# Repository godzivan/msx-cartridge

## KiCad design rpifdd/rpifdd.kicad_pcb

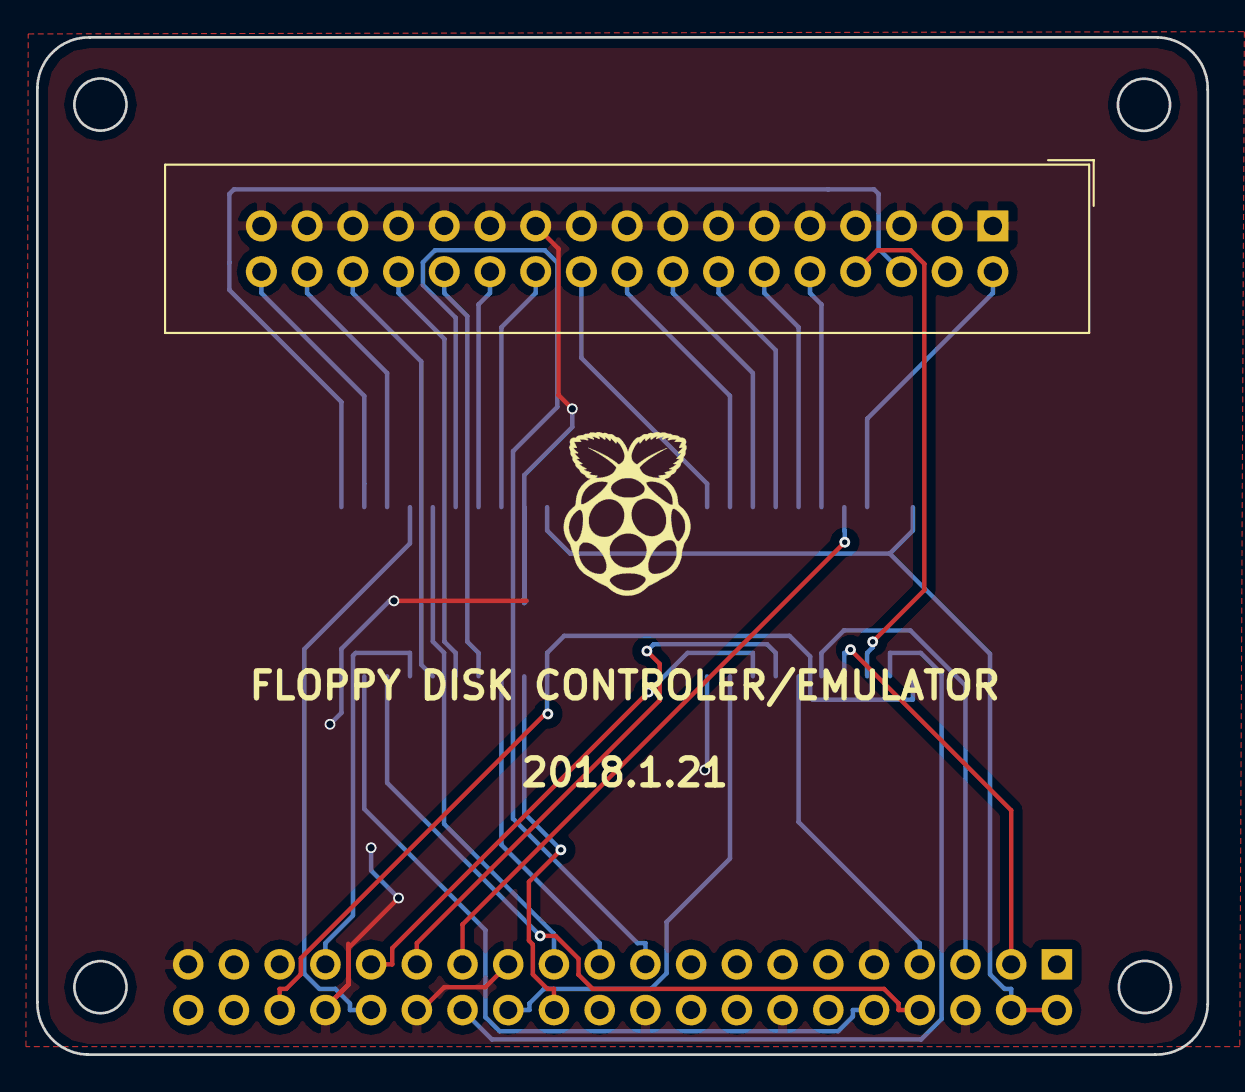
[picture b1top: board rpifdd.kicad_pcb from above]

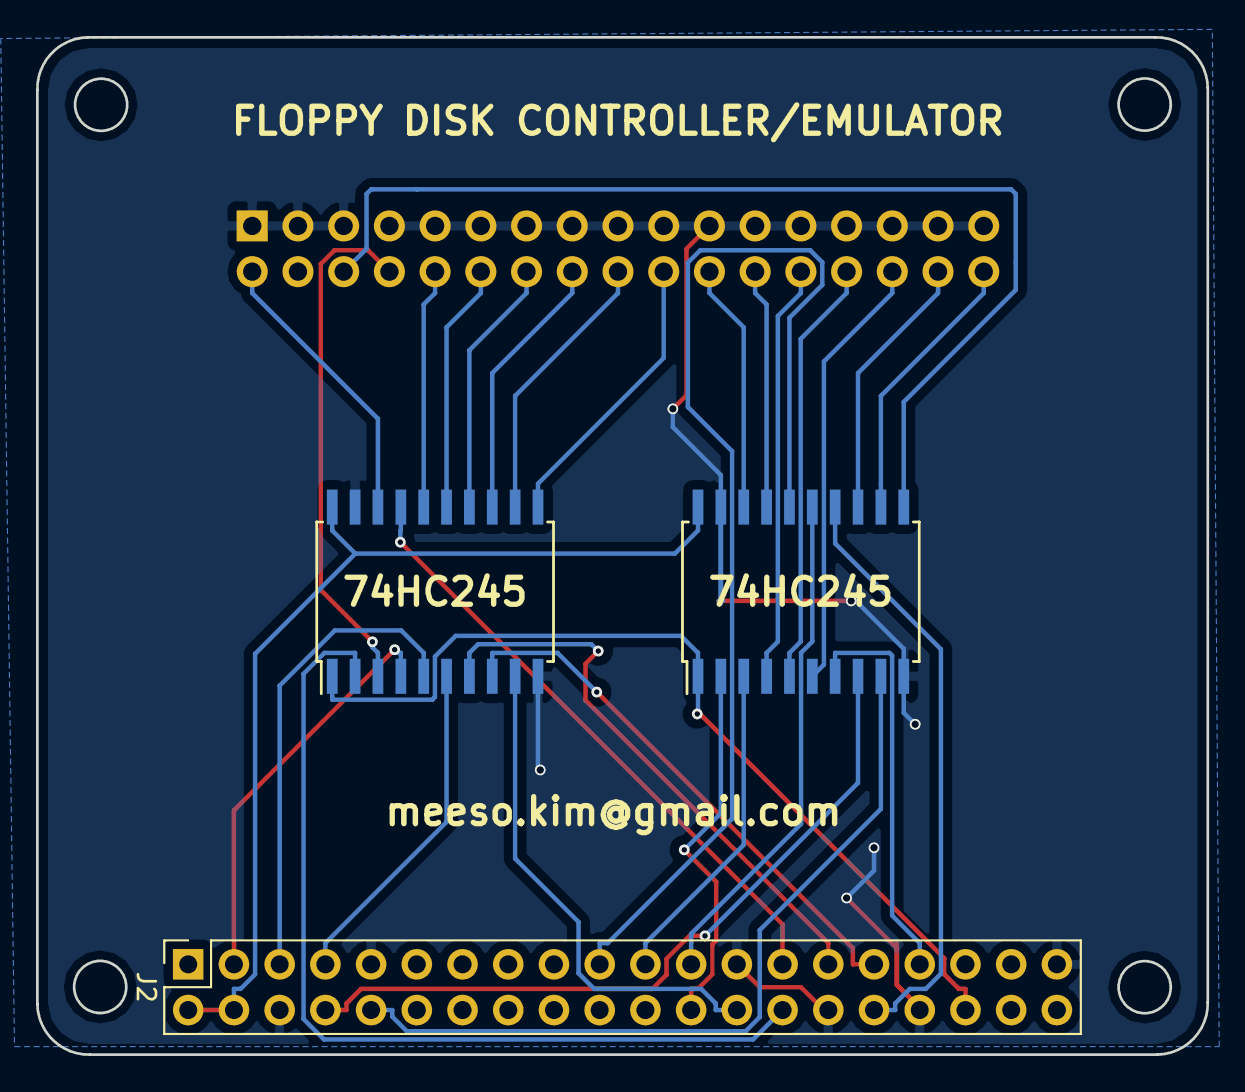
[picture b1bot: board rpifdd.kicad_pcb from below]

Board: 2 copper layers, 65.0 x 56.5 mm, 4 parts (3 on the bottom side), 35 nets.

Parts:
J1: FDD_Connector; IDC-Header_2x17_Pitch2.54mm_Straight
J2: Raspberry_Pi_2_3; Socket_Strip_Straight_2x20_Pitch2.54mm
U1, U2: 74HC245; SOIC-20W_7.5x12.8mm_Pitch1.27mm

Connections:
+5V: J2.2, J2.4, U1.20, U2.20
/DIR: J1.18, U1.12
/DRSEL3: J1.6, U2.11
/DRSELA: J1.12, U1.15
/DRSELB: J1.14, U1.14
/DSKCHG: J1.34, U2.12
/INDEX: J1.8, U1.3
/MODESEL: J1.2, U1.18
/MOTEA: J1.10, U1.16
/MOTEB: J1.16, U1.13
/R0: J2.28, U1.2
/R1: J2.27, U1.17
/R2: J2.3, U1.4
/R3: J2.5, U1.5
/R4: J2.7, U1.6
/R5: J2.29, U1.7
/R6: J2.31, U1.8
/R7: J2.26, U1.9
/R8: J2.24, U2.2
/R9: J2.21, U2.3
/R10: J2.19, U2.16
/R11: J2.23, U2.15
/R12: J2.32, U2.14
/R13: J2.33, U2.7
/R14: J2.8, U2.8
/R15: J2.10, U2.9
/R16: J2.36, U1.1, U2.1
/RDATA: J1.30, U2.6
/SIDE1: J1.32, U2.13
/STEP: J1.20, U1.11
/TRK00: J1.26, U2.4
/WDATA: J1.22, U2.18
/WGATE: J1.24, U2.17
/WPT: J1.28, U2.5
GND: J1.1, J1.3, J1.5, J1.7, J1.9, J1.11, J1.13, J1.15, J1.17, J1.19, J1.21, J1.23, J1.25, J1.27, J1.29, J1.31, J1.33, J2.6, J2.9, J2.14, J2.20, J2.25, J2.30, J2.34, J2.39, U1.10, U1.19, U2.10, U2.19

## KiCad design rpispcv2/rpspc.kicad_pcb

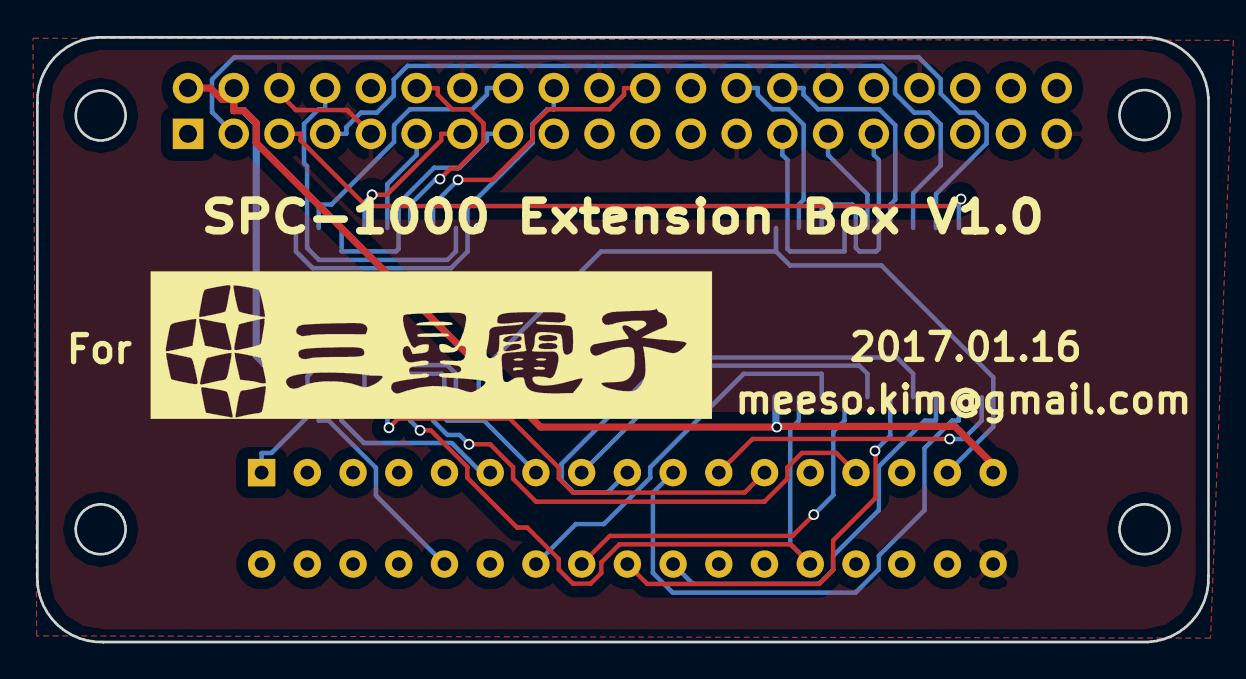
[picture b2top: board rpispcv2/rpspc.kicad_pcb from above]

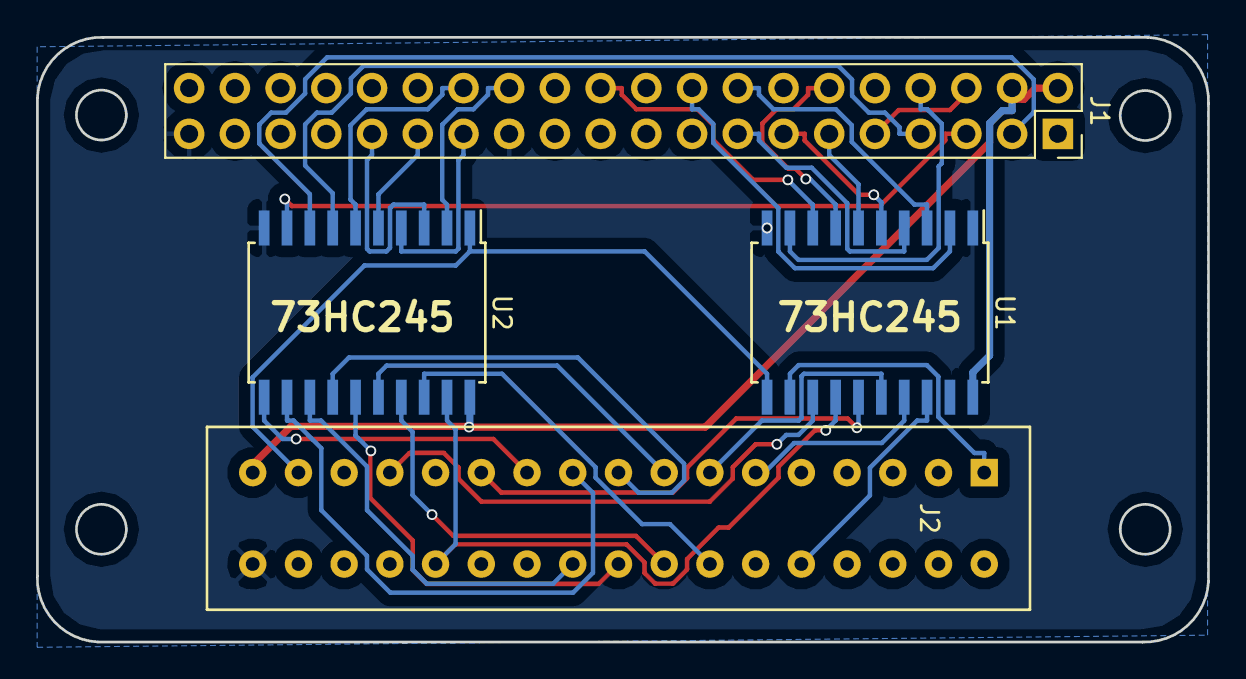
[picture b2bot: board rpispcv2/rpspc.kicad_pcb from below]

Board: 2 copper layers, 65.1 x 33.6 mm, 4 parts (4 on the bottom side), 34 nets.

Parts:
J1: RPi_GPIO; Socket_Strip_Straight_2x20_Pitch2.54mm
J2: Conn_02x17_Top_Bottom; cardedge_female_2x17_2.54mm
U1, U2: 74LS245; SOIC-20W_7.5x12.8mm_Pitch1.27mm

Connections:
+5V: J1.2, J1.4, J2.33, U1.20, U2.20
/A0: J2.13, U1.16
/A1: J2.11, U1.17
/A6: J2.1, U1.12
/A11: J2.10, U1.18
/CLK: J2.27, U1.13
/D0: J2.15, U2.16
/D1: J2.17, U2.14
/D2: J2.19, U2.12
/D3: J2.21, U2.11
/D4: J2.20, U2.13
/D5: J2.18, U2.15
/D6: J2.16, U2.17
/D7: J2.14, U2.18
/EXT1: J2.26, U1.14, U2.19
/RA0: J1.15, U1.4
/RA1: J1.16, U1.3
/RA2: J1.18, U1.2
/RA4: J1.22, U1.8
/RCLK: J1.12, U1.7
/RD0: J1.27, U2.4
/RD1: J1.28, U2.6
/RD2: J1.3, U2.8
/RD3: J1.5, U2.9
/RD4: J1.7, U2.7
/RD5: J1.29, U2.5
/RD6: J1.31, U2.3
/RD7: J1.26, U2.2
/RESET: J2.23, U1.15
/REXT1: J1.11, U1.6
/RRESET: J1.13, U1.5
/RWR: J1.8, U1.9
/WR: J2.31, U1.11, U2.1
GND: J1.6, J1.9, J1.14, J1.20, J1.25, J1.30, J1.34, J1.39, J2.34, U1.1, U1.10, U1.19, U2.10

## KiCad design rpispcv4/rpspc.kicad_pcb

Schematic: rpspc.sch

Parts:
J1, J3: RPi_GPIO; Pin_Header_Straight_2x20_Pitch2.54mm
J2: Conn_02x17_Top_Bottom; Socket_Strip_Straight_2x20_Pitch2.54mm
U1: LVC4245; SOIC-24W_7.5x15.4mm_Pitch1.27mm
U2: 74HC244; SOIC-20W_7.5x12.8mm_Pitch1.27mm

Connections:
+5V: J1.2, J1.4, J2.33, J3.2, J3.4, U1.1
/A0: J2.13, U2.15
/A1: J2.11, U2.13
/A2: J2.9
/A3: J2.7
/A4: J2.5
/A5: J2.3
/A6: J2.1, U2.4
/A7: J2.4
/A8: J2.6
/A9: J2.8
/A10: J2.12
/A11: J2.10, U2.11
/A12: J2.2
/CLK: J2.27, U2.6
/D0: J2.15, U1.8
/D1: J2.17, U1.6
/D2: J2.19, U1.4
/D3: J2.21, U1.3
/D4: J2.20, U1.5
/D5: J2.18, U1.7
/D6: J2.16, U1.9
/D7: J2.14, U1.10
/EXT1: J2.26, U1.22, U2.8
/RA0: J1.15, J3.15, U2.5
/RA1: J1.16, J3.16, U2.7
/RA2: J1.18, J3.18, U2.9
/RA4: J1.22, J3.22, U2.16
/RCLK: J1.12, J3.12, U2.14
/RD: J2.30, U1.2
/RD0: J1.27, J3.27, U1.16
/RD1: J1.28, J3.28, U1.18
/RD2: J1.3, J3.3, U1.20
/RD3: J1.5, J3.5, U1.21
/RD4: J1.7, J3.7, U1.19
/RD5: J1.29, J3.29, U1.17
/RD6: J1.31, J3.31, U1.15
/RD7: J1.26, J3.26, U1.14
/RESET: J2.23, U2.17
/REXT1: J1.11, J3.11, U2.12
/RRESET: J1.13, J3.13, U2.3
/RWR: J1.8, J3.8, U2.18
/VCC: J1.1, J3.1, U1.23, U1.24, U2.20
/WR: J2.31, U2.2
GND: J1.6, J1.9, J1.14, J1.20, J1.25, J1.30, J1.34, J2.34, J3.6, J3.9, J3.14, J3.20, J3.25, J3.30, J3.34, U1.11, U1.12, U1.13, U2.1, U2.10, U2.19

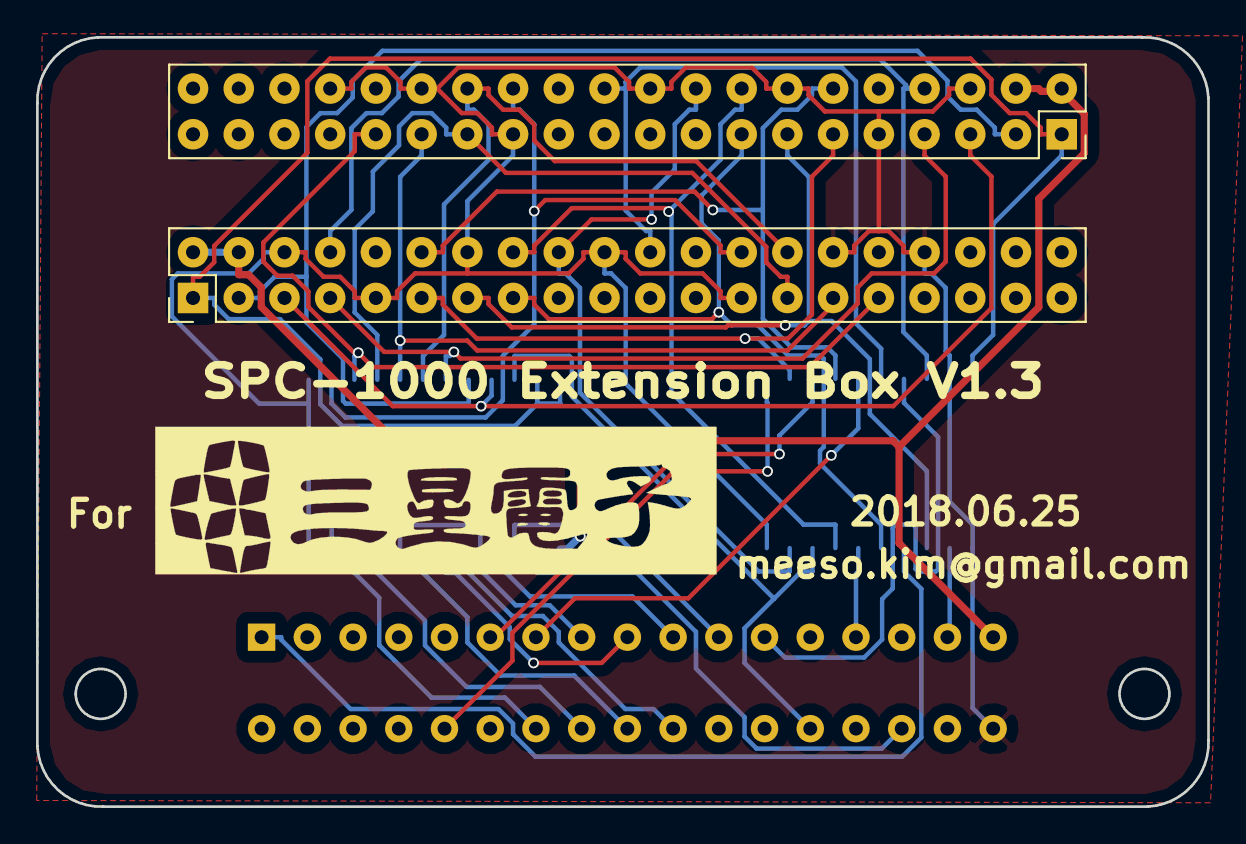
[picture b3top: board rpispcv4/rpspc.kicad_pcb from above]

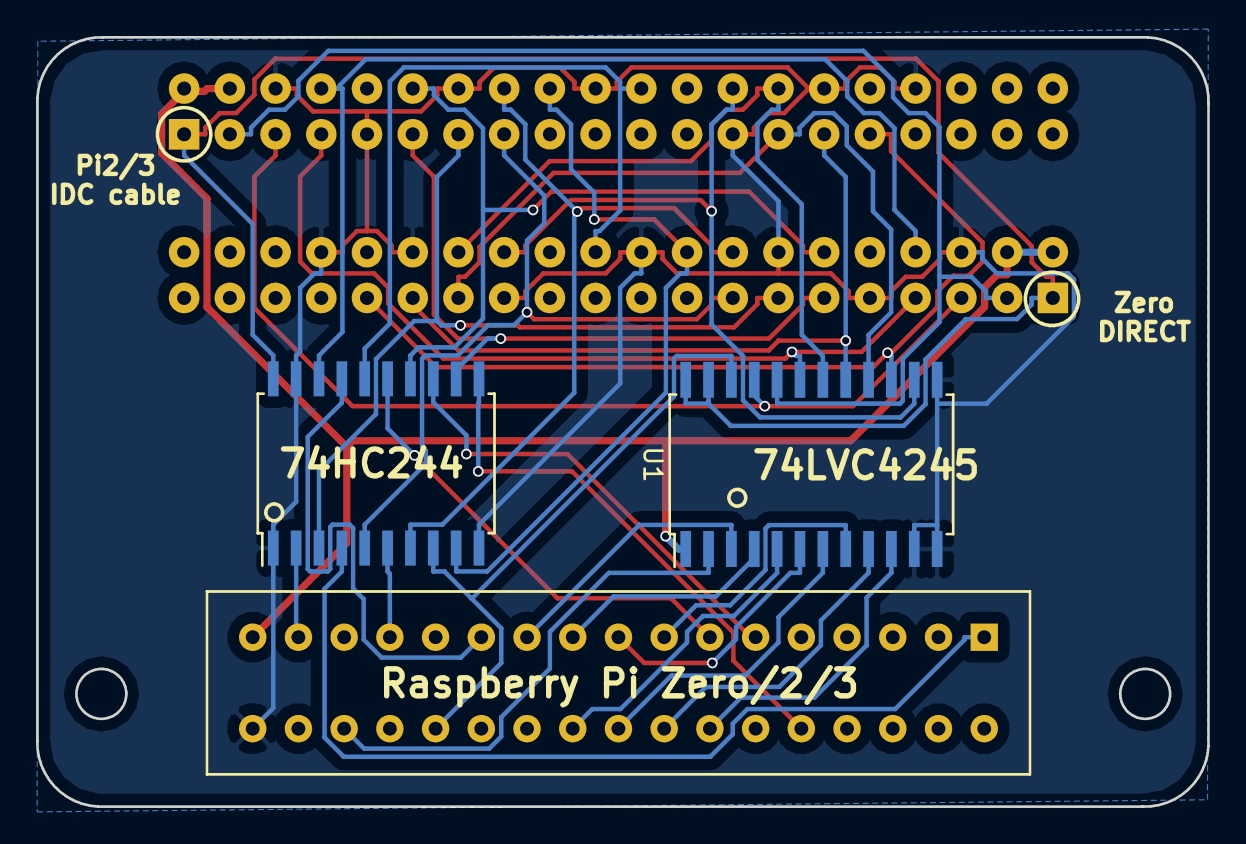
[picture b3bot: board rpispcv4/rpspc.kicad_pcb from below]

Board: 2 copper layers, 65.1 x 42.7 mm, 5 parts (3 on the bottom side), 36 nets.

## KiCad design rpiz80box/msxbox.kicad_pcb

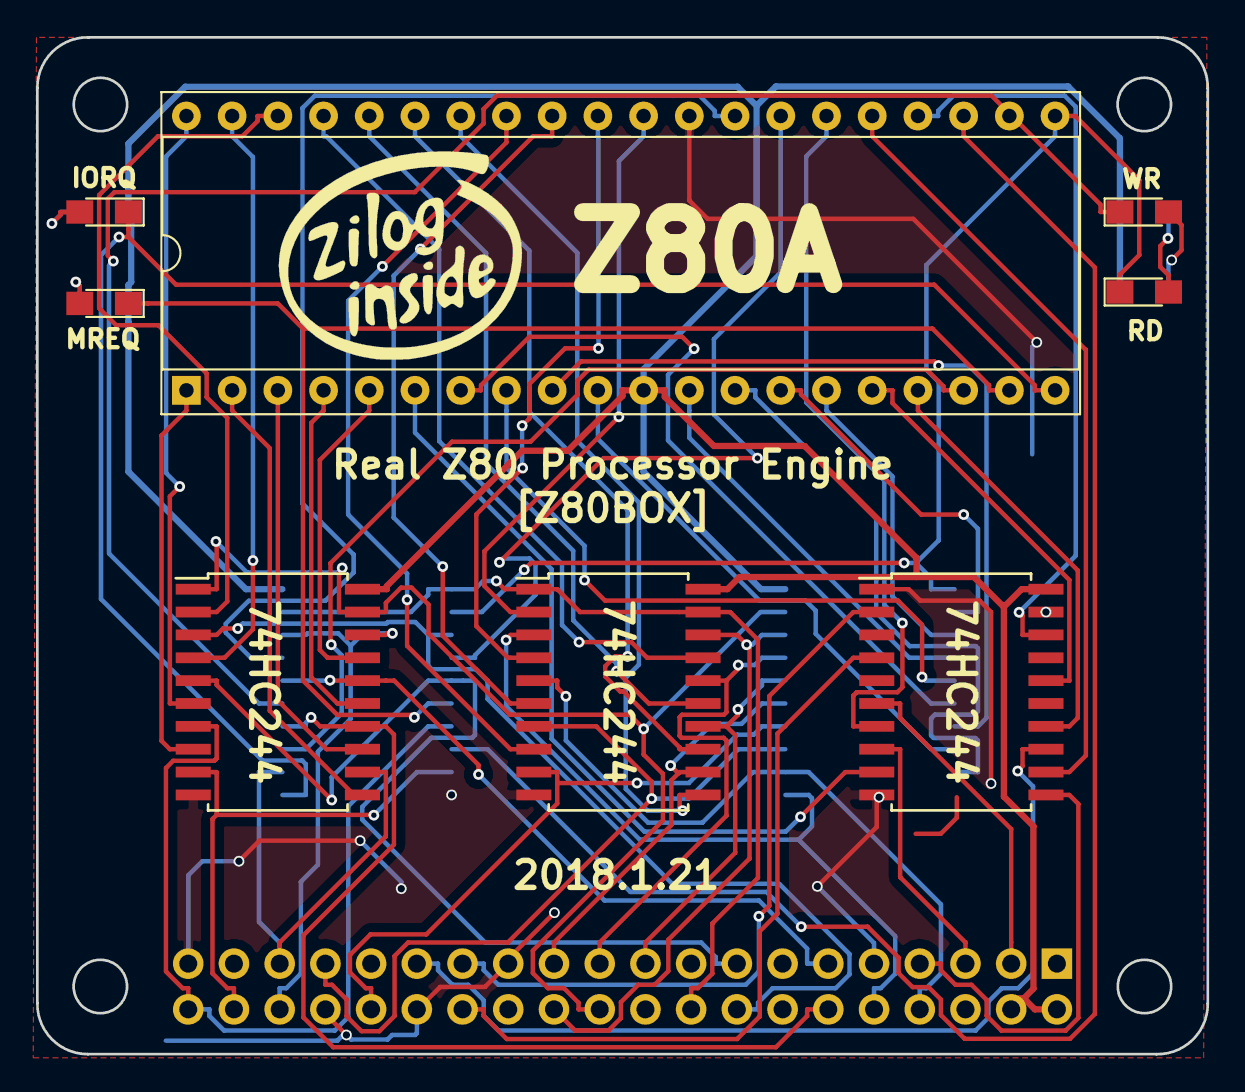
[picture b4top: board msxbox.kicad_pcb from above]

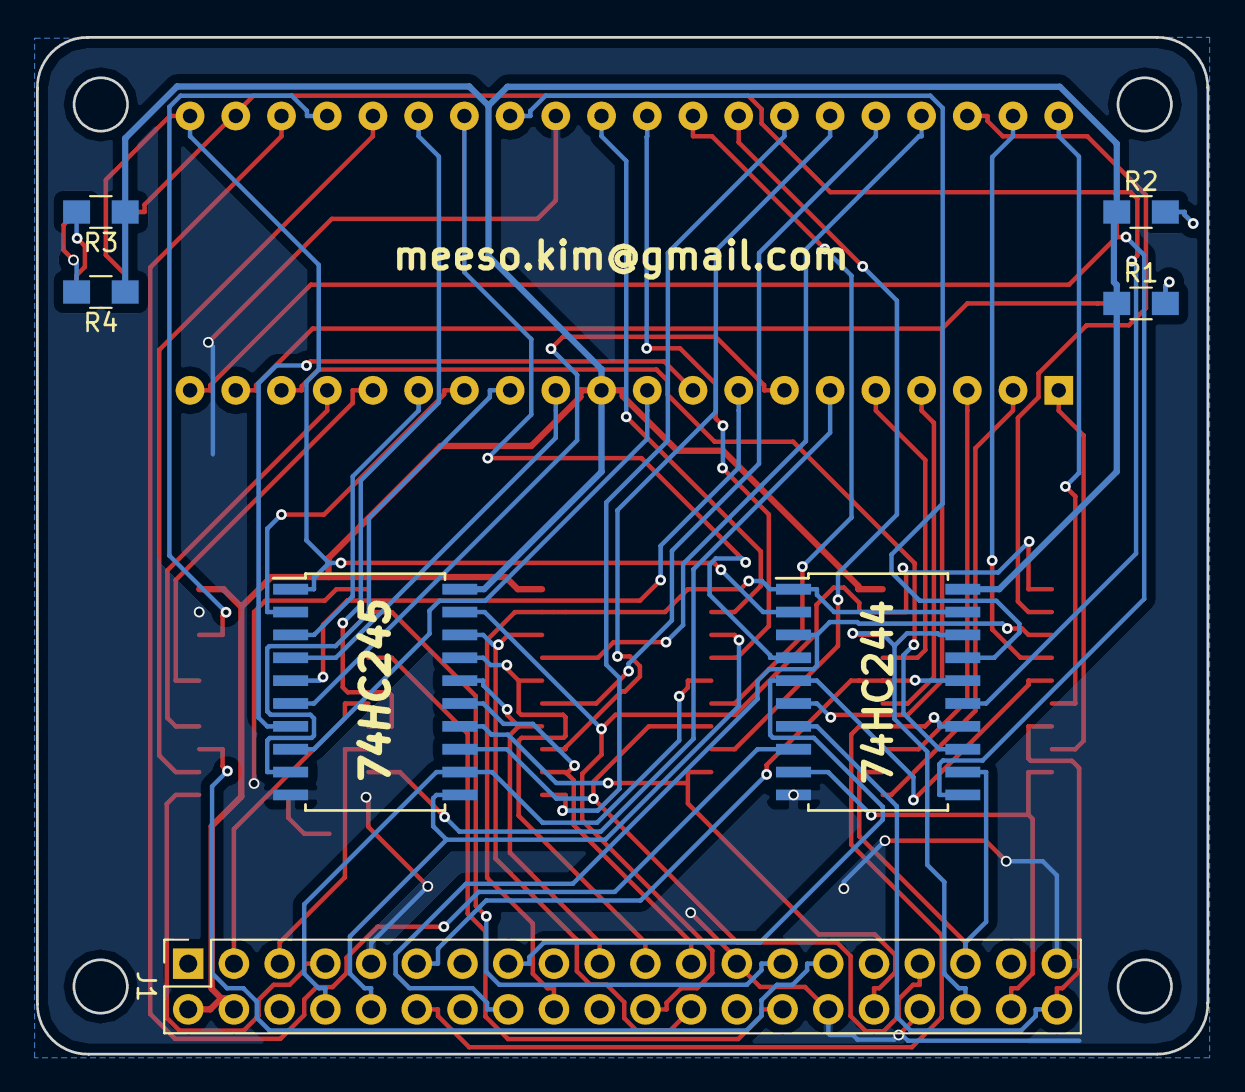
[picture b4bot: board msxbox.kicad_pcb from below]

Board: 2 copper layers, 65.0 x 56.5 mm, 15 parts (7 on the bottom side), 68 nets.

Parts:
D1, D2, D3, D4: LED_Small; LED_0805_HandSoldering
J1: Raspberry_Pi_2_3; Socket_Strip_Straight_2x20_Pitch2.54mm
R1, R2, R3, R4: R; R_0805_HandSoldering
U1: Z80CPU; DIP-40_W15.24mm_Socket
U2, U3, U5, U6: 74LS244; SOIC-20W_7.5x12.8mm_Pitch1.27mm
U4: 74HC245; SOIC-20W_7.5x12.8mm_Pitch1.27mm

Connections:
+5V: J1.2, J1.4, R1.1, R2.1, R3.1, R4.1, U1.11, U2.20, U3.20, U4.20, U5.20, U6.20
/A0: U1.30, U6.2
/A1: U1.31, U6.4
/A2: U1.32, U6.6
/A3: U1.33, U6.8
/A4: U1.34, U6.11
/A5: U1.35, U6.13
/A6: U1.36, U6.15
/A7: U1.37, U6.17
/A8: U1.38, U3.2
/A9: U1.39, U3.4
/A10: U1.40, U3.6
/A11: U1.1, U3.8
/A12: U1.2, U3.11
/A13: U1.3, U3.13
/A14: U1.4, U3.15
/A15: U1.5, U3.17
/BUSACK: U1.23, U5.8
/BUSRQ: U1.25, U2.12
/CLK: U1.6, U2.9
/D0: U1.14, U4.2
/D1: U1.15, U4.3
/D2: U1.12, U4.4
/D3: U1.8, U4.5
/D4: U1.7, U4.6
/D5: U1.9, U4.7
/D6: U1.10, U4.8
/D7: U1.13, U4.9
/HALT: U1.18, U5.13
/INT: U1.16, U2.16
/M1: U1.27, U5.4
/NMI: U1.17, U2.14
/R0: J1.24, U4.18, U6.18
/R1: J1.21, U4.17, U6.16
/R2: J1.19, U4.16, U6.14
/R3: J1.23, U4.15, U6.12
/R4: J1.32, U4.14, U6.9
/R5: J1.33, U4.13, U6.7
/R6: J1.8, U4.12, U6.5
/R7: J1.10, U4.11, U6.3
/R8: J1.36, U3.18, U5.18
/R9: J1.11, U3.16, U5.16
/R10: J1.12, U3.14, U5.14
/R11: J1.35, U3.12, U5.12
/R12: J1.38, U3.9, U5.9
/R13: J1.40, U3.7, U5.7
/R14: J1.15, U3.5, U5.5
/R15: J1.16, U3.3, U5.3
/R16: J1.27, U2.2
/R17: J1.28, U2.4
/R18: J1.3, U2.6
/R19: J1.5, U2.8
/R20: J1.29, U2.13
/RCLK: J1.7, U2.11
/RESET: U1.26, U2.7
/RFSH: U1.28, U5.17
/RLE0: J1.18, U5.1, U5.19, U6.1, U6.19
/RLE1: J1.22, U3.1, U3.19, U4.19
/WAIT: U1.24, U2.18
GND: J1.6, J1.9, J1.14, J1.20, J1.25, J1.30, J1.34, J1.39, U1.29, U2.1, U2.10, U2.19, U3.10, U4.10, U5.10, U6.10
IORQ: D2.1, U1.20, U5.11
MERQ: D1.1, U1.19, U5.6
unnamed: D1.2, R1.2
unnamed: D2.2, R2.2
unnamed: D3.2, R3.2
unnamed: D4.2, R4.2
RD: D3.1, U1.21, U4.1, U5.2
WR: D4.1, U1.22, U5.15
